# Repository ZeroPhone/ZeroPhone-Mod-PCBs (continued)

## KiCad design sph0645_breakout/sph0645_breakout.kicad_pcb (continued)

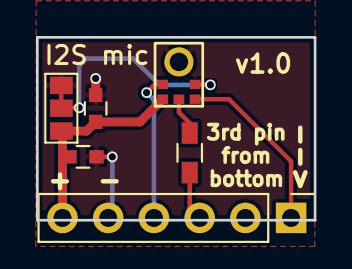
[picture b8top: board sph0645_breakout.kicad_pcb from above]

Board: 2 copper layers, 15.4 x 10.2 mm, 6 parts (0 on the bottom side), 6 nets.
